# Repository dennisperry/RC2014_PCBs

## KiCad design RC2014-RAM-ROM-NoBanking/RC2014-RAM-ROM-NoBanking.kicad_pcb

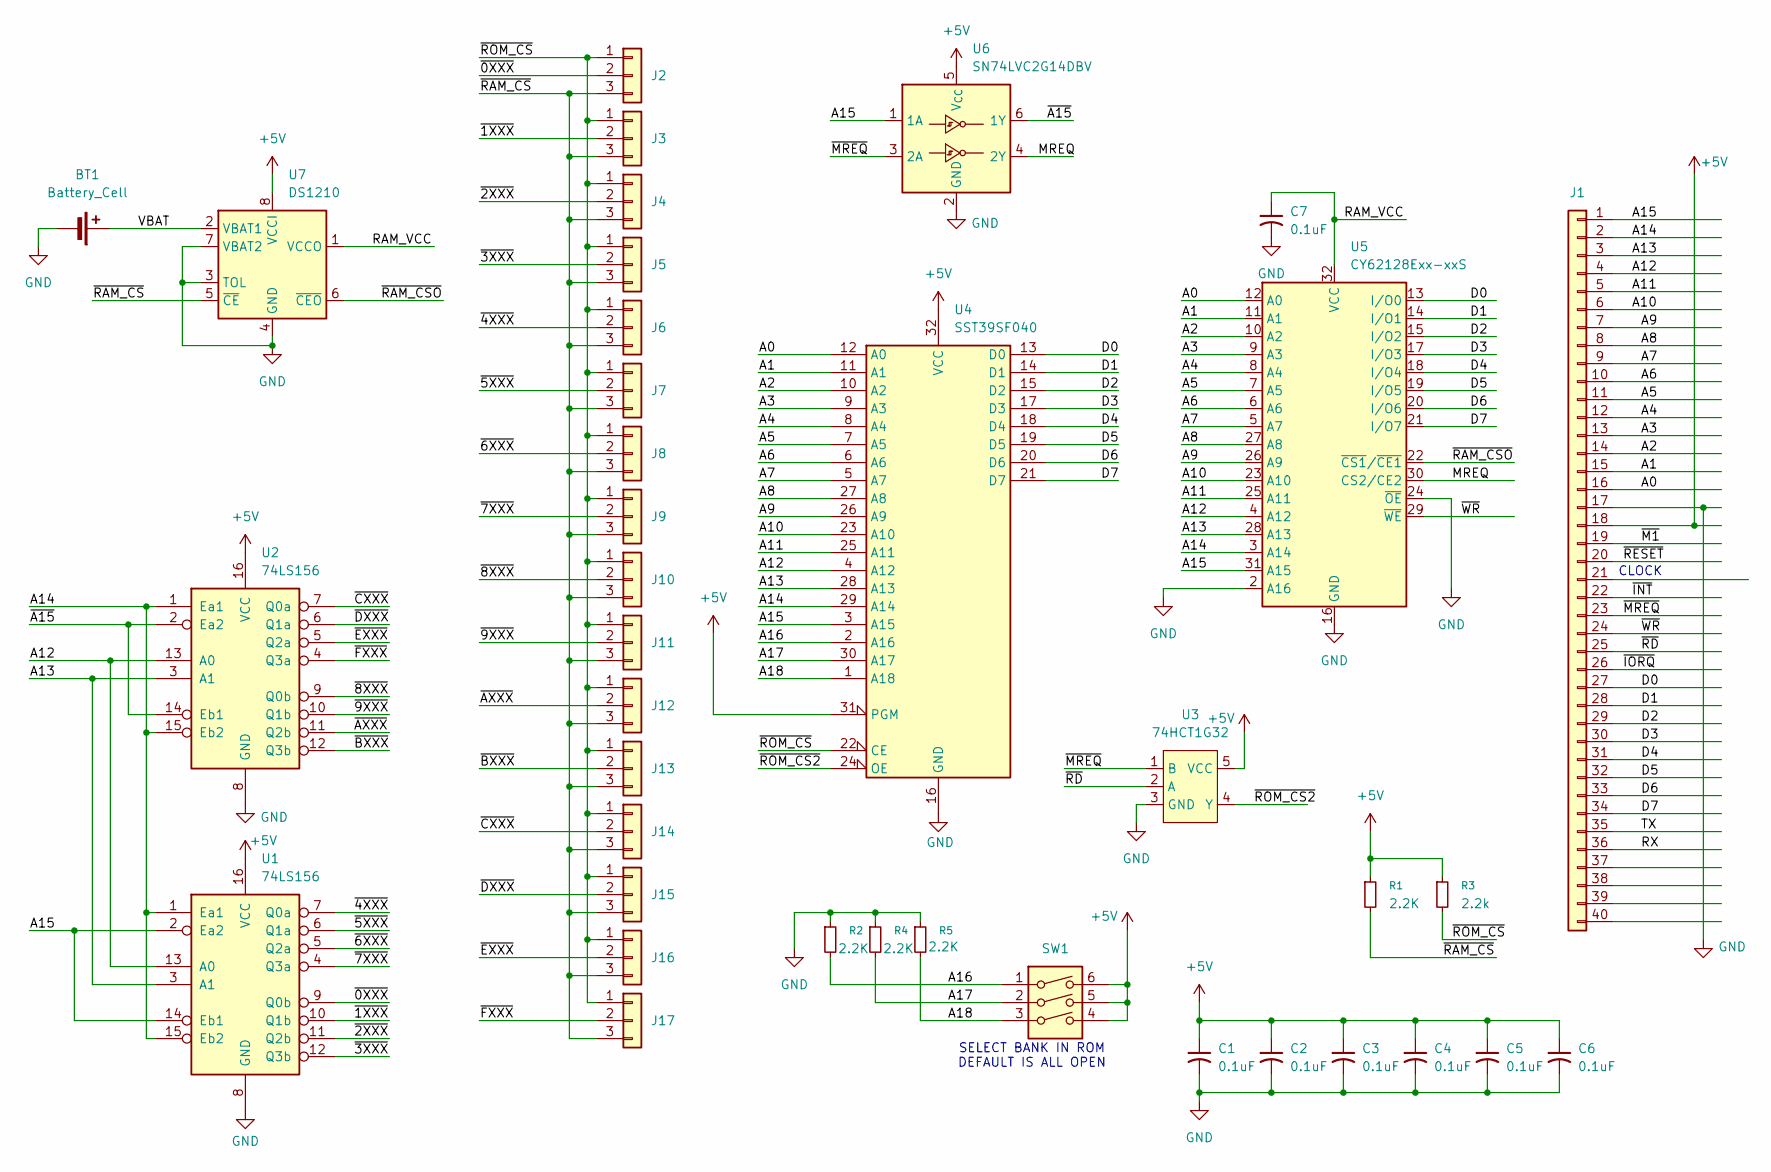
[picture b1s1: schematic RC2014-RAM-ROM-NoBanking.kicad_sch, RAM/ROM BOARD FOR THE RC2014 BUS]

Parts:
BT1: Battery_Cell; Battery_Holder_CR2032_Universal
C1, C2, C3, C4, C5, C6, C7: 0.1uF; C_0805_2012Metric_Pad1.18x1.45mm_HandSolder
J1: Conn_01x40; PinHeader_1x40_P2.54mm_Vertical
J2, J3, J4, J5, J6, J7, J8, J9, J10, J11, J12, J13, J14, J15, J16, J17: Conn_01x03; PinHeader_1x03_P2.54mm_Vertical-dp
R1, R2, R4, R5: 2.2K; R_0805_2012Metric_Pad1.20x1.40mm_HandSolder
R3: 2.2k; R_0805_2012Metric_Pad1.20x1.40mm_HandSolder
SW1: SW_DIP_x03; SW_DIP_SPSTx03_Slide_9.78x9.8mm_W7.62mm_P2.54mm
U1, U2: 74LS156; SOP-16_4.55x10.3mm_P1.27mm
U3: 74HCT1G32; SOT-23-5_HandSoldering
U4: SST39SF040; DIP_Socket-32_W11.9mm_W12.7mm_W15.24mm_W17.78mm_W18.5mm_3M_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
U5: CY62128Exx-xxS; SOP-32_11.305x20.495mm_P1.27mm
U6: SN74LVC2G14DBV; SOT-23-6
U7: DS1210; DIP-8_W7.62mm

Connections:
+5V: C1.1, C2.1, C3.1, C4.1, C5.1, C6.1, J1.18, R1.1, R3.1, SW1.4, SW1.5, SW1.6, U1.16 (VCC), U2.16 (VCC), U3.5 (VCC), U4.31 (PGM), U4.32 (VCC), U6.5 (V_{CC}), U7.8 (VCCI)
/A0: J1.16, U4.12 (A0), U5.12 (A0)
/A1: J1.15, U4.11 (A1), U5.11 (A1)
/A2: J1.14, U4.10 (A2), U5.10 (A2)
/A3: J1.13, U4.9 (A3), U5.9 (A3)
/A4: J1.12, U4.8 (A4), U5.8 (A4)
/A5: J1.11, U4.7 (A5), U5.7 (A5)
/A6: J1.10, U4.6 (A6), U5.6 (A6)
/A7: J1.9, U4.5 (A7), U5.5 (A7)
/A8: J1.8, U4.27 (A8), U5.27 (A8)
/A9: J1.7, U4.26 (A9), U5.26 (A9)
/A10: J1.6, U4.23 (A10), U5.23 (A10)
/A11: J1.5, U4.25 (A11), U5.25 (A11)
/A12: J1.4, U1.13 (A0), U2.13 (A0), U4.4 (A12), U5.4 (A12)
/A13: J1.3, U1.3 (A1), U2.3 (A1), U4.28 (A13), U5.28 (A13)
/A14: J1.2, U1.1 (Ea1), U1.15 (Eb2), U2.1 (Ea1), U2.15 (Eb2), U4.29 (A14), U5.3 (A14)
/A15: J1.1, U1.2 (Ea2), U1.14 (Eb1), U4.3 (A15), U5.31 (A15), U6.1 (1A)
/A16: R2.2, SW1.1, U4.2 (A16)
/A17: R4.2, SW1.2, U4.30 (A17)
/A18: R5.2, SW1.3, U4.1 (A18)
/D0: J1.27, U4.13 (D0), U5.13 (I/O0)
/D1: J1.28, U4.14 (D1), U5.14 (I/O1)
/D2: J1.29, U4.15 (D2), U5.15 (I/O2)
/D3: J1.30, U4.17 (D3), U5.17 (I/O3)
/D4: J1.31, U4.18 (D4), U5.18 (I/O4)
/D5: J1.32, U4.19 (D5), U5.19 (I/O5)
/D6: J1.33, U4.20 (D6), U5.20 (I/O6)
/D7: J1.34, U4.21 (D7), U5.21 (I/O7)
/MREQ: U5.30 (CS2/CE2), U6.4 (2Y)
/RAM_VCC: C7.1, U5.32 (VCC), U7.1 (VCCO)
/RX: J1.36
/TX: J1.35
/VBAT: BT1.1 (+), U7.2 (VBAT1)
/~0XXX: J2.2, U1.9 (Q0b)
/~1XXX: J3.2, U1.10 (Q1b)
/~2XXX: J4.2, U1.11 (Q2b)
/~3XXX: J5.2, U1.12 (Q3b)
/~4XXX: J6.2, U1.7 (Q0a)
/~5XXX: J7.2, U1.6 (Q1a)
/~6XXX: J8.2, U1.5 (Q2a)
/~7XXX: J9.2, U1.4 (Q3a)
/~8XXX: J10.2, U2.9 (Q0b)
/~9XXX: J11.2, U2.10 (Q1b)
/~A15: U2.2 (Ea2), U2.14 (Eb1), U6.6 (1Y)
/~AXXX: J12.2, U2.11 (Q2b)
/~BXXX: J13.2, U2.12 (Q3b)
/~CXXX: J14.2, U2.7 (Q0a)
/~DXXX: J15.2, U2.6 (Q1a)
/~EXXX: J16.2, U2.5 (Q2a)
/~FXXX: J17.2, U2.4 (Q3a)
/~INT: J1.22
/~IORQ: J1.26
/~M1: J1.19
/~MREQ: J1.23, U3.1 (B), U6.3 (2A)
/~RAM_CSO: U5.22 (~CS1/~CE1), U7.6 (~CEO)
/~RAM_CS: J2.3, J3.3, J4.3, J5.3, J6.3, J7.3, J8.3, J9.3, J10.3, J11.3, J12.3, J13.3, J14.3, J15.3, J16.3, J17.3, R1.2, U7.5 (~CE)
/~RD: J1.25, U3.2 (A)
/~RESET: J1.20
/~ROM_CS2: U3.4 (Y), U4.24 (OE)
/~ROM_CS: J2.1, J3.1, J4.1, J5.1, J6.1, J7.1, J8.1, J9.1, J10.1, J11.1, J12.1, J13.1, J14.1, J15.1, J16.1, J17.1, R3.2, U4.22 (CE)
/~WR: J1.24, U5.29 (~WE)
GND: BT1.2 (-), C1.2, C2.2, C3.2, C4.2, C5.2, C6.2, C7.2, J1.17, R2.1, R4.1, R5.1, U1.8 (GND), U2.8 (GND), U3.3 (GND), U4.16 (GND), U5.2 (A16), U5.16 (GND), U5.24 (~OE), U6.2 (GND), U7.3 (TOL), U7.4 (GND), U7.7 (VBAT2)

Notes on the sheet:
CLOCK
SELECT BANK IN ROM DEFAULT IS ALL OPEN

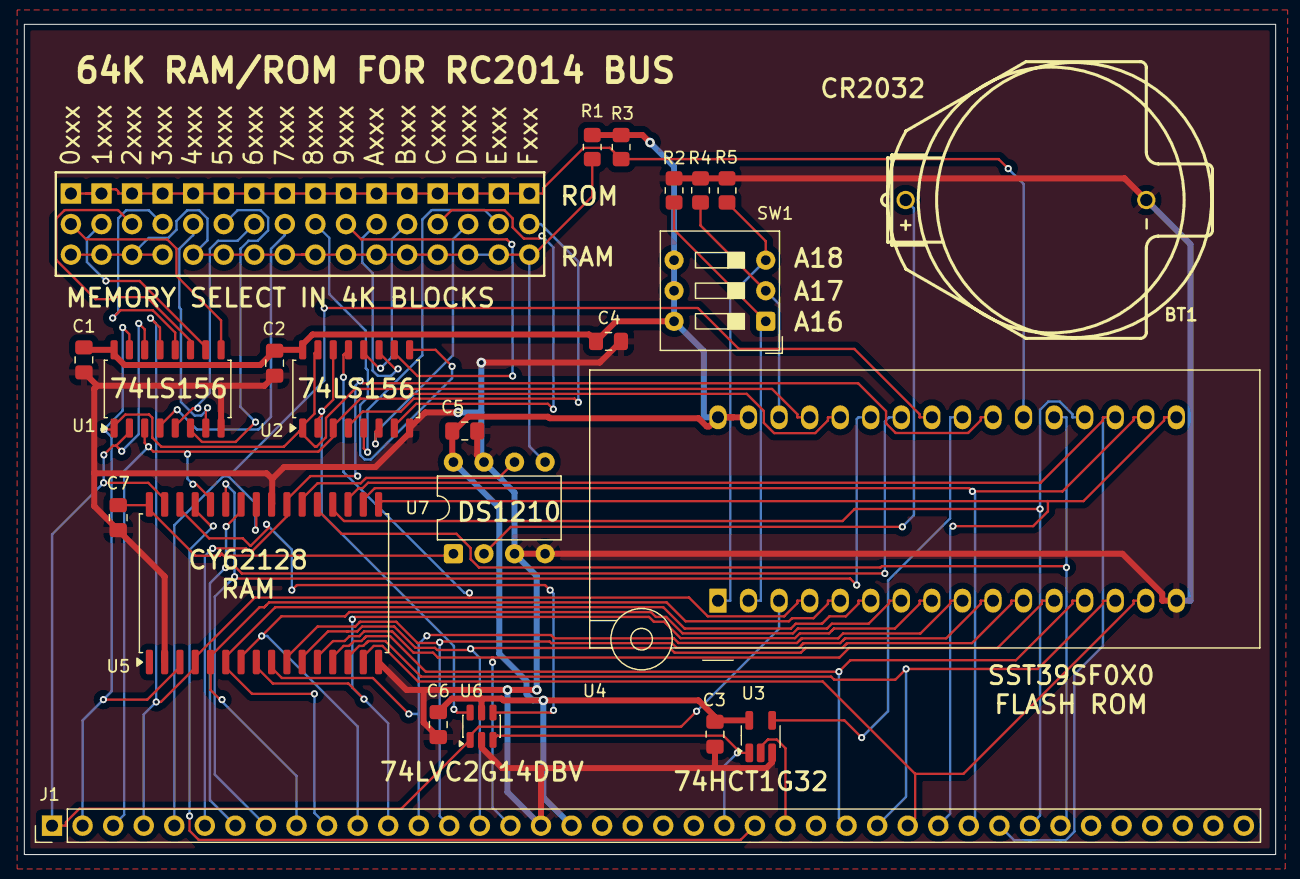
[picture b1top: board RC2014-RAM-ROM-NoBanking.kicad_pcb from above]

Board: 2 copper layers, 104.0 x 69.0 mm, 38 parts (0 on the bottom side), 56 nets.
